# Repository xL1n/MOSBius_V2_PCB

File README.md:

MOSBius V2 PCB Design 
Contains Mother Board & Daughter Board

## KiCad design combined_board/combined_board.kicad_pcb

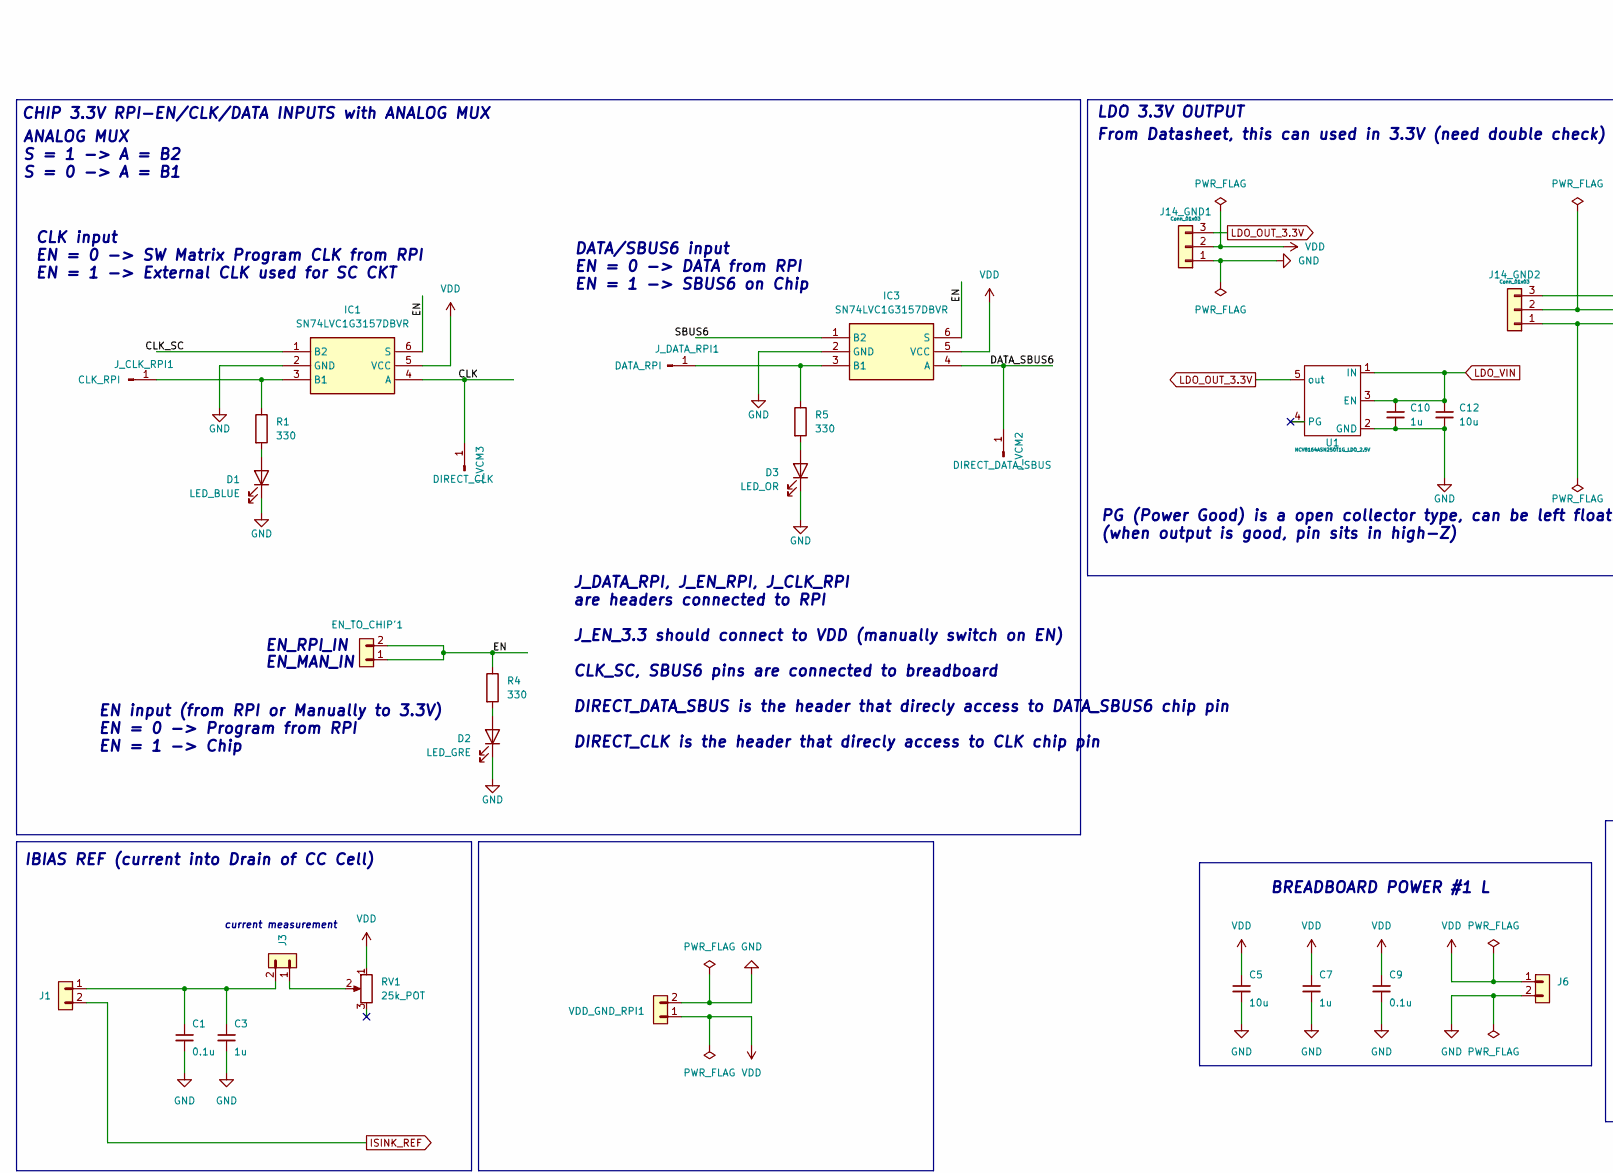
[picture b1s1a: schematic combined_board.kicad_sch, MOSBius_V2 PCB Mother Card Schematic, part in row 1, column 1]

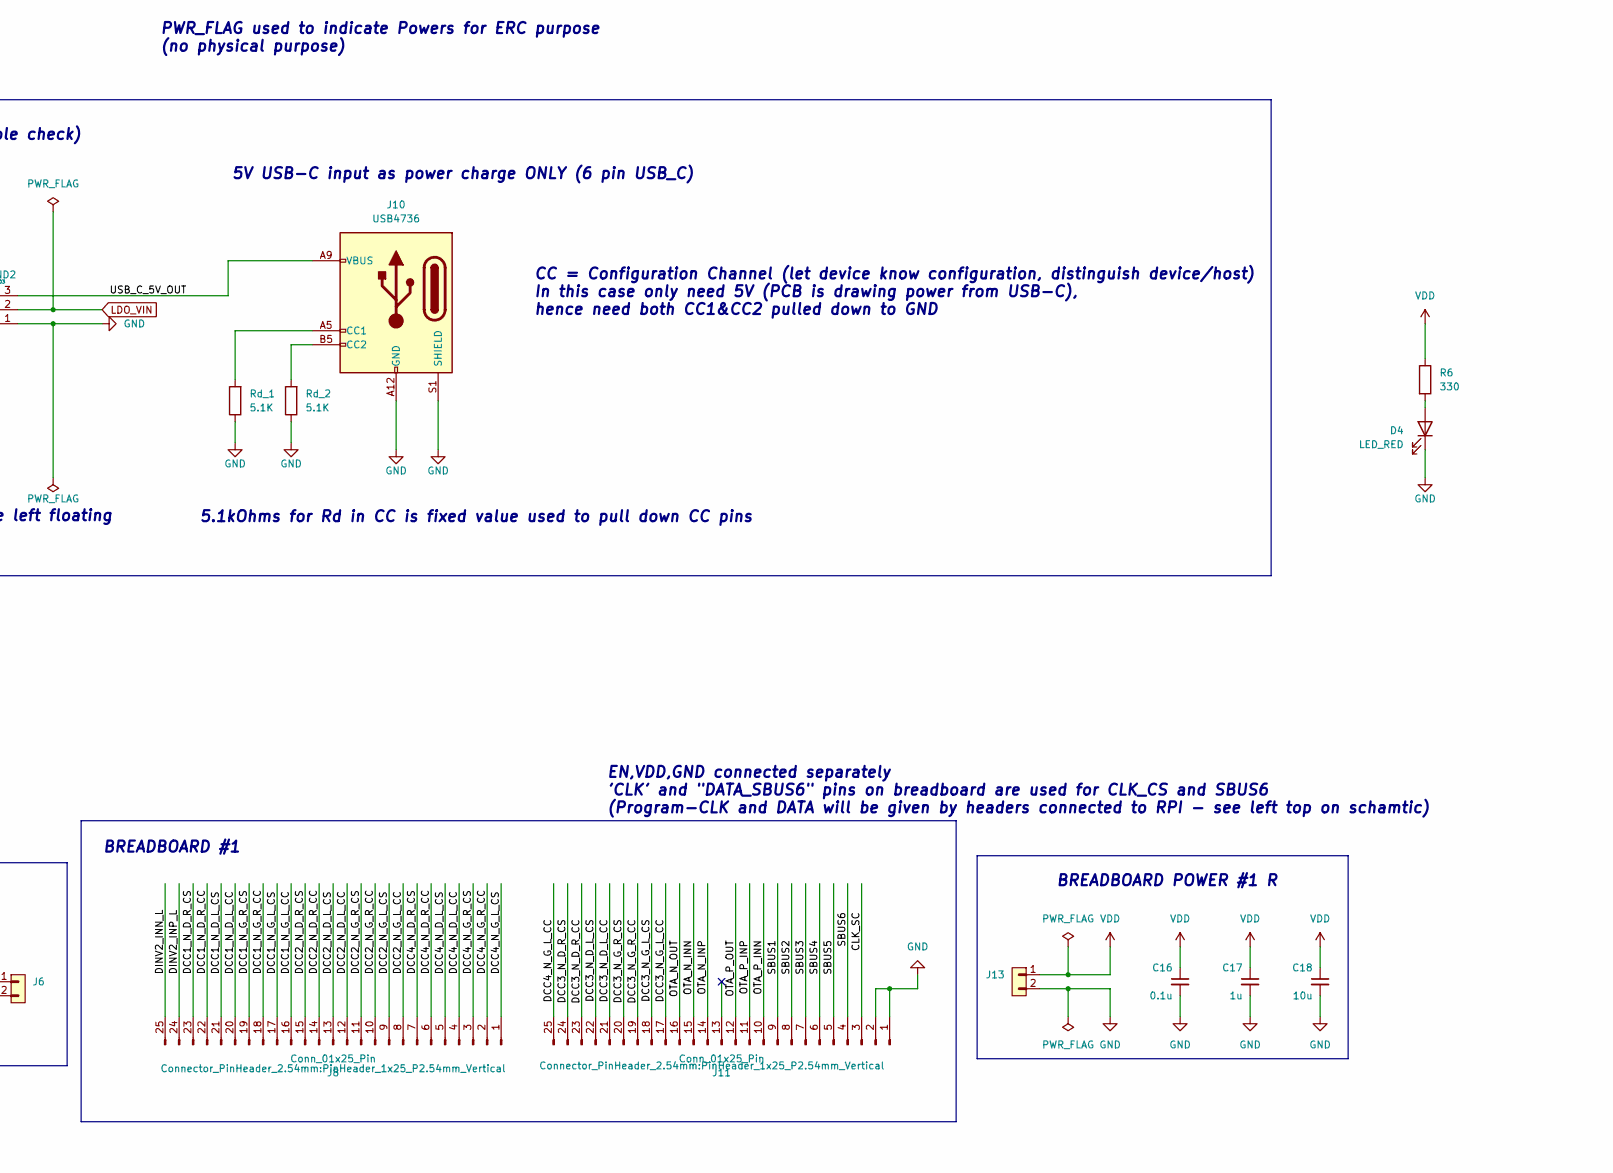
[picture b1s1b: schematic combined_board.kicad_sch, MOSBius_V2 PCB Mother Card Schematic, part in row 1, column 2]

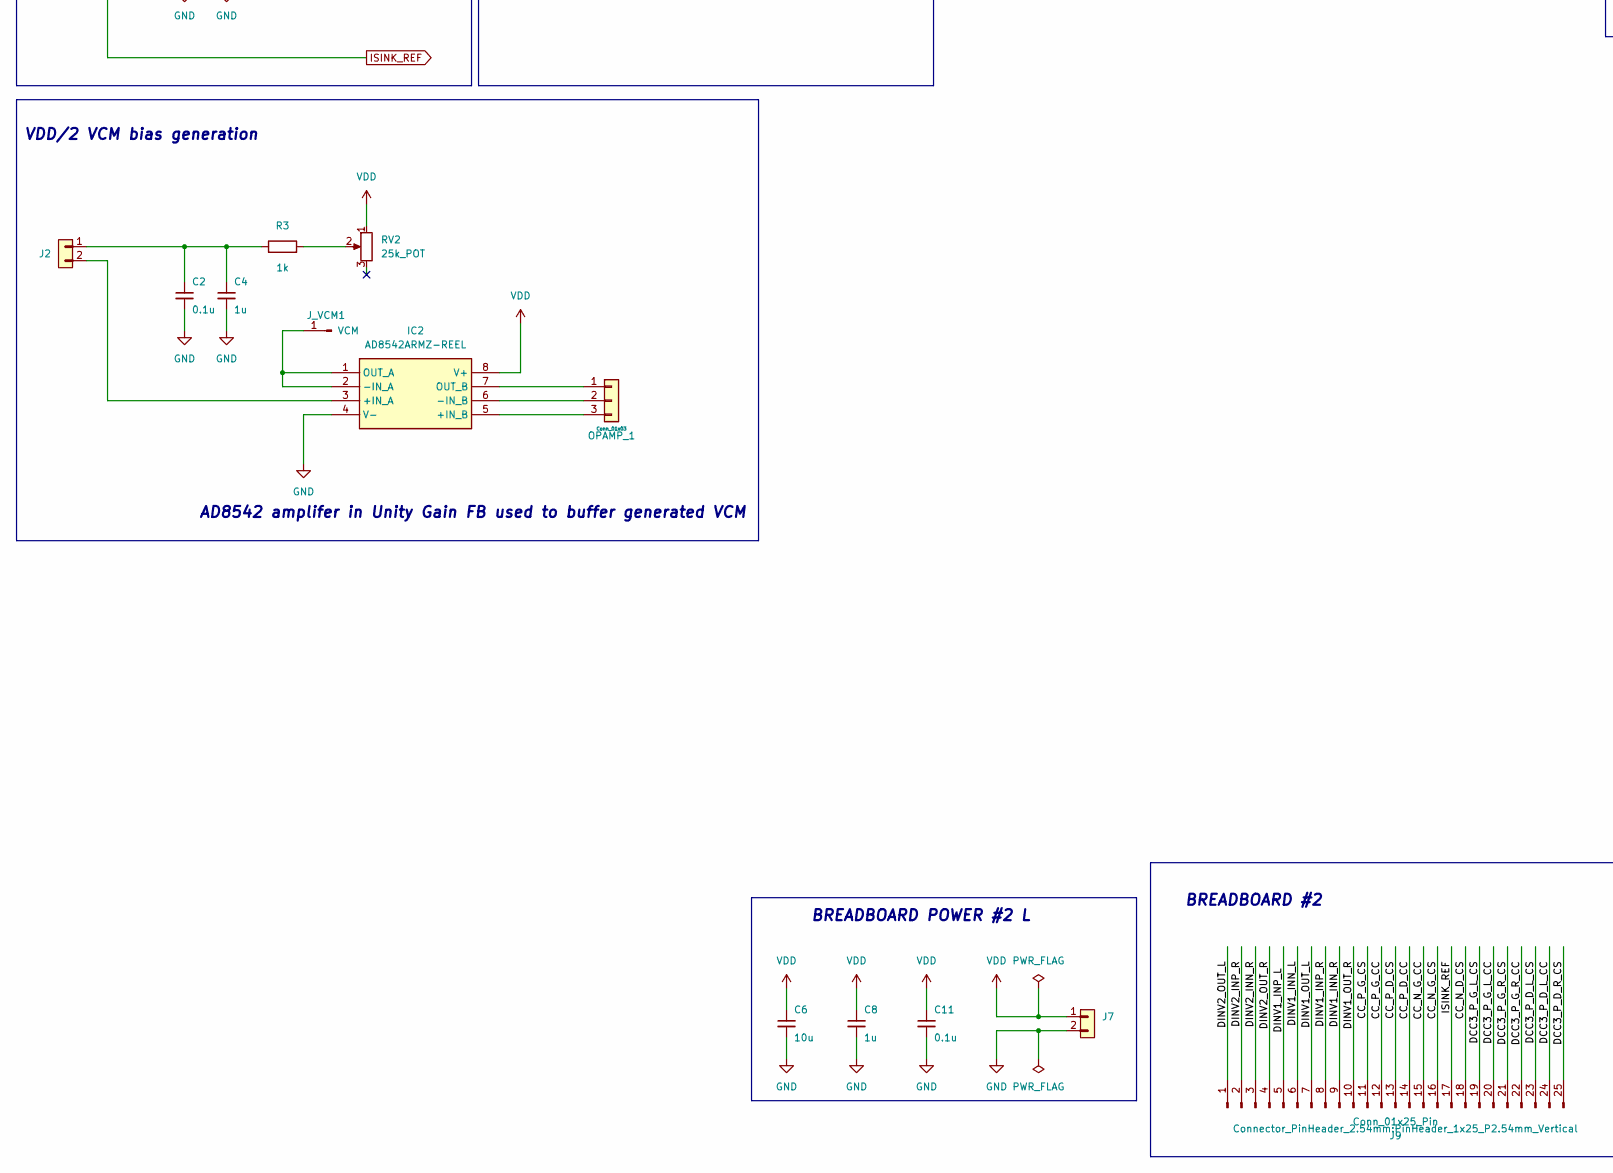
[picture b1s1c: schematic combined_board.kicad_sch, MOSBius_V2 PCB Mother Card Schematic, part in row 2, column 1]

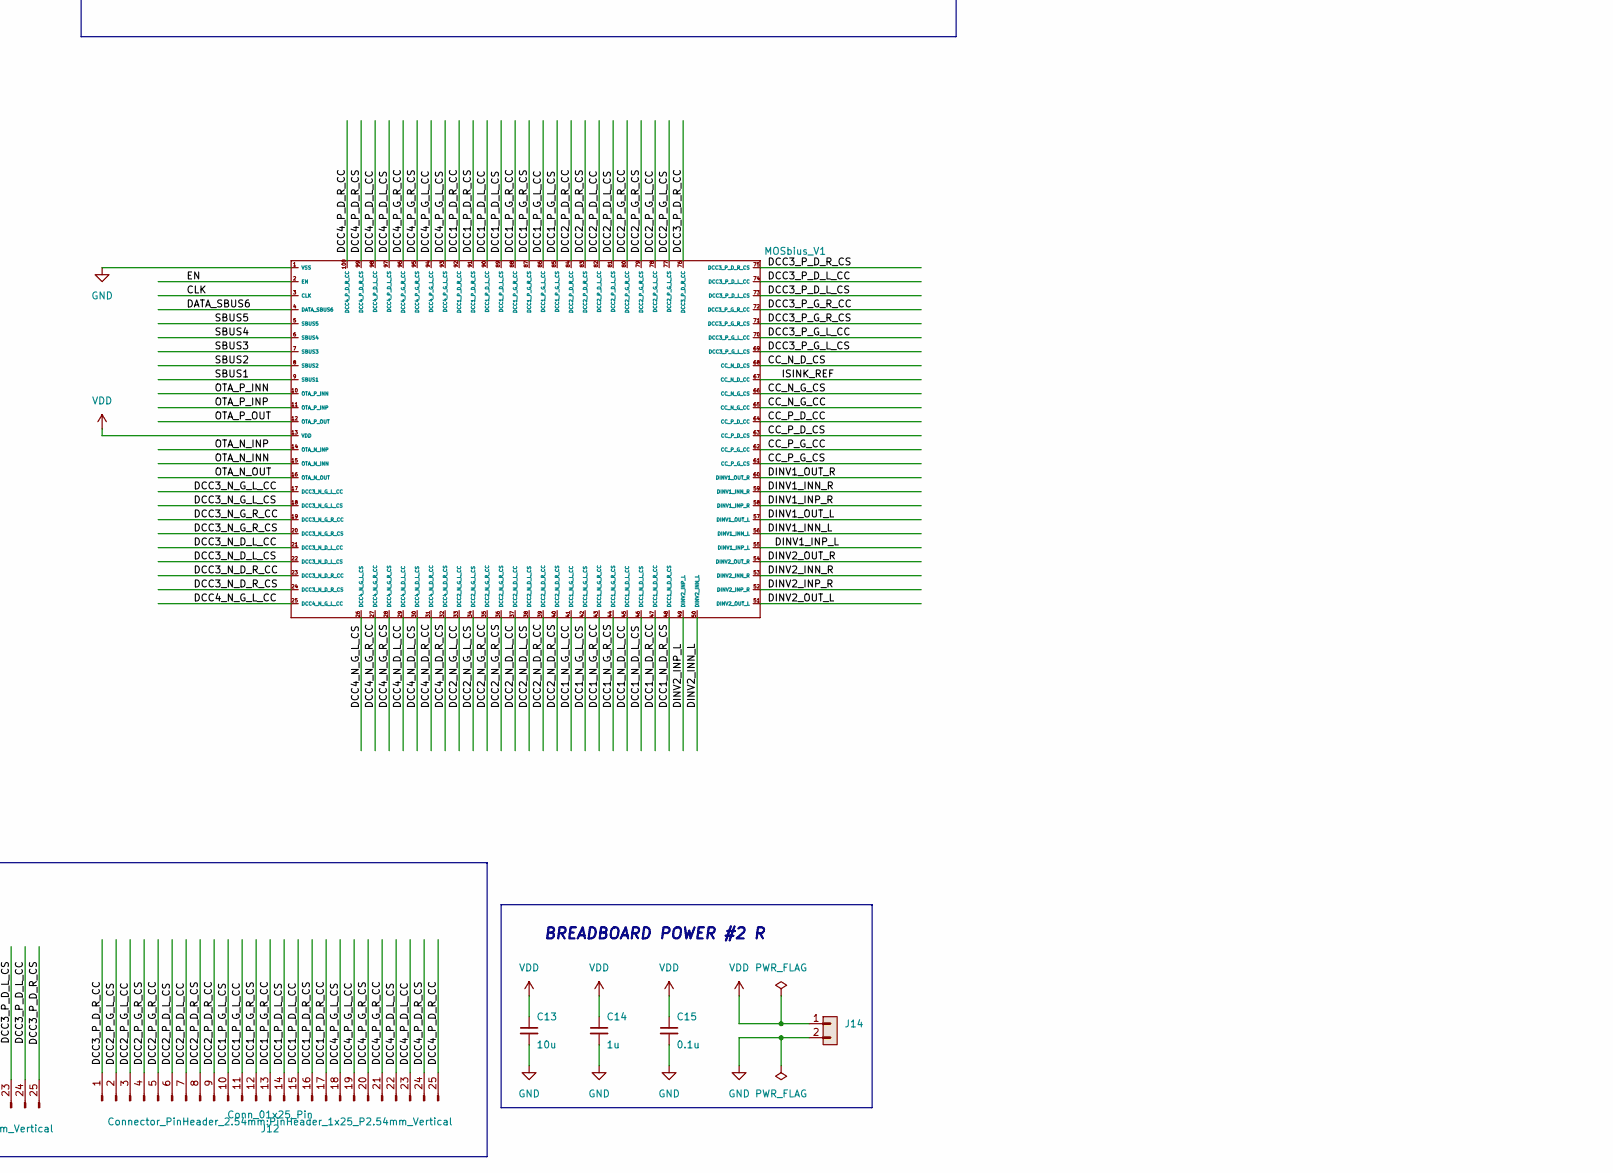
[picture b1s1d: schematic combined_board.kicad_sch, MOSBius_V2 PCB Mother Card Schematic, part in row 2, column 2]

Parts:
C1, C2, C9, C11, C15, C16: 0.1u; C_0603_1608Metric
C3, C4, C7, C8, C10, C14, C17: 1u; C_0603_1608Metric
C5, C6, C12, C13, C18: 10u; C_0603_1608Metric
D1: LED_BLUE; LED_150120RS75000_WRE
D2: LED_GRE; LED_150120RS75000_WRE
D3: LED_OR; LED_150120RS75000_WRE
D4: LED_RED; LED_150120RS75000_WRE
EN_TO_CHIP'1: PINHD_1x2_Male; PinHeader_1x02_P2.54mm_Vertical
IC1, IC3: SN74LVC1G3157DBVR; SN74LVC1G3157; Manufacturer_Part_Number SN74LVC1G3157DBVR; Mouser Part Number 595-SN74LVC1G3157DBV
IC2: AD8542ARMZ-REEL; AD8542; Manufacturer_Part_Number AD8542ARMZ-REEL; Mouser Part Number 584-AD8542ARMZ-R
J1, J2, J3, J6, J7, J14: PINHD_1x2_Male; PinHeader_1x02_P2.54mm_Vertical
J8, J9, J11, J12: Conn_01x25_Pin; PinHeader_1x25_P2.54mm_Vertical
J10: USB4736; USB_C_Receptacle_GCT_USB4125-xx-x_6P_TopMnt_Horizontal
J13: Conn_01x02_Pin; PinHeader_1x02_P2.54mm_Vertical
J14_GND1, J14_GND2: Conn_01x03; PinHeader_1x03_P2.54mm_Vertical
J_CLK_RPI1: CLK_RPI; PinHeader_1x01_P2.54mm_Vertical
J_DATA_RPI1: DATA_RPI; PinHeader_1x01_P2.54mm_Vertical
J_VCM1: VCM; PinHeader_1x01_P2.54mm_Vertical
J_VCM2: DIRECT_DATA_SBUS; PinHeader_1x01_P2.54mm_Vertical
J_VCM3: DIRECT_CLK; PinHeader_1x01_P2.54mm_Vertical
MOSbius_V1: MOSbius_V2; ArtInChip_QFN-100-1EP_12x12mm_P0.4mm_EP7.4x7.4mm
OPAMP_1: Conn_01x03; PinHeader_1x03_P2.54mm_Vertical
R1, R4, R5, R6: 330; R_0603_1608Metric
R3: 1k; R_0603_1608Metric
RV1, RV2: 25k_POT; Potentiometer_Bourns_3266Y_Vertical
Rd_1, Rd_2: 5.1K; R_0603_1608Metric
U1: NCV8164ASN250T1G_LDO_2.5V; NCV8164ASN250T1G_LDO
VDD_GND_RPI1: PINHD_1x2_Male; PinHeader_1x02_P2.54mm_Vertical

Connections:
/CC_N_D_CS: J9.18, MOSbius_V1.68 (CC_N_D_CS); also elsewhere on the board
/CC_N_G_CC: J9.15, MOSbius_V1.65 (CC_N_G_CC); also elsewhere on the board
/CC_N_G_CS: J9.16, MOSbius_V1.66 (CC_N_G_CS); also elsewhere on the board
/CC_P_D_CC: J9.14, MOSbius_V1.64 (CC_P_D_CC); also elsewhere on the board
/CC_P_D_CS: J9.13, MOSbius_V1.63 (CC_P_D_CS); also elsewhere on the board
/CC_P_G_CC: J9.12, MOSbius_V1.62 (CC_P_G_CC); also elsewhere on the board
/CC_P_G_CS: J9.11, MOSbius_V1.61 (CC_P_G_CS); also elsewhere on the board
/CLK: IC1.4 (A), J_VCM3.1, MOSbius_V1.3 (CLK); also elsewhere on the board
/CLK_SC: IC1.1 (B2), J11.3
/DATA_SBUS6: IC3.4 (A), J_VCM2.1, MOSbius_V1.4 (DATA_SBUS6); also elsewhere on the board
/DCC1_N_D_L_CC: J8.20, MOSbius_V1.45 (DCC1_N_D_L_CC); also elsewhere on the board
/DCC1_N_D_L_CS: J8.21, MOSbius_V1.46 (DCC1_N_D_L_CS); also elsewhere on the board
/DCC1_N_D_R_CC: J8.22, MOSbius_V1.47 (DCC1_N_D_R_CC); also elsewhere on the board
/DCC1_N_D_R_CS: J8.23, MOSbius_V1.48 (DCC1_N_D_R_CS); also elsewhere on the board
/DCC1_N_G_L_CC: J8.16, MOSbius_V1.41 (DCC1_N_G_L_CC); also elsewhere on the board
/DCC1_N_G_L_CS: J8.17, MOSbius_V1.42 (DCC1_N_G_L_CS); also elsewhere on the board
/DCC1_N_G_R_CC: J8.18, MOSbius_V1.43 (DCC1_N_G_R_CC); also elsewhere on the board
/DCC1_N_G_R_CS: J8.19, MOSbius_V1.44 (DCC1_N_G_R_CS); also elsewhere on the board
/DCC1_P_D_L_CC: J12.15, MOSbius_V1.90 (DCC1_P_D_L_CC); also elsewhere on the board
/DCC1_P_D_L_CS: J12.14, MOSbius_V1.89 (DCC1_P_D_L_CS); also elsewhere on the board
/DCC1_P_D_R_CC: J12.17, MOSbius_V1.92 (DCC1_P_D_R_CC); also elsewhere on the board
/DCC1_P_D_R_CS: J12.16, MOSbius_V1.91 (DCC1_P_D_R_CS); also elsewhere on the board
/DCC1_P_G_L_CC: J12.11, MOSbius_V1.86 (DCC1_P_G_L_CC); also elsewhere on the board
/DCC1_P_G_L_CS: J12.10, MOSbius_V1.85 (DCC1_P_G_L_CS); also elsewhere on the board
/DCC1_P_G_R_CC: J12.13, MOSbius_V1.88 (DCC1_P_G_R_CC); also elsewhere on the board
/DCC1_P_G_R_CS: J12.12, MOSbius_V1.87 (DCC1_P_G_R_CS); also elsewhere on the board
/DCC2_N_D_L_CC: J8.12, MOSbius_V1.37 (DCC2_N_D_L_CC); also elsewhere on the board
/DCC2_N_D_L_CS: J8.13, MOSbius_V1.38 (DCC2_N_D_L_CS); also elsewhere on the board
/DCC2_N_D_R_CC: J8.14, MOSbius_V1.39 (DCC2_N_D_R_CC); also elsewhere on the board
/DCC2_N_D_R_CS: J8.15, MOSbius_V1.40 (DCC2_N_D_R_CS); also elsewhere on the board
/DCC2_N_G_L_CC: J8.8, MOSbius_V1.33 (DCC2_N_G_L_CC); also elsewhere on the board
/DCC2_N_G_L_CS: J8.9, MOSbius_V1.34 (DCC2_N_G_L_CS); also elsewhere on the board
/DCC2_N_G_R_CC: J8.10, MOSbius_V1.35 (DCC2_N_G_R_CC); also elsewhere on the board
/DCC2_N_G_R_CS: J8.11, MOSbius_V1.36 (DCC2_N_G_R_CS); also elsewhere on the board
/DCC2_P_D_L_CC: J12.7, MOSbius_V1.82 (DCC2_P_D_L_CC); also elsewhere on the board
/DCC2_P_D_L_CS: J12.6, MOSbius_V1.81 (DCC2_P_D_L_CS); also elsewhere on the board
/DCC2_P_D_R_CC: J12.9, MOSbius_V1.84 (DCC2_P_D_R_CC); also elsewhere on the board
/DCC2_P_D_R_CS: J12.8, MOSbius_V1.83 (DCC2_P_D_R_CS); also elsewhere on the board
/DCC2_P_G_L_CC: J12.3, MOSbius_V1.78 (DCC2_P_G_L_CC); also elsewhere on the board
/DCC2_P_G_L_CS: J12.2, MOSbius_V1.77 (DCC2_P_G_L_CS); also elsewhere on the board
/DCC2_P_G_R_CC: J12.5, MOSbius_V1.80 (DCC2_P_G_R_CC); also elsewhere on the board
/DCC2_P_G_R_CS: J12.4, MOSbius_V1.79 (DCC2_P_G_R_CS); also elsewhere on the board
/DCC3_N_D_L_CC: J11.21, MOSbius_V1.21 (DCC3_N_D_L_CC); also elsewhere on the board
/DCC3_N_D_L_CS: J11.22, MOSbius_V1.22 (DCC3_N_D_L_CS); also elsewhere on the board
/DCC3_N_D_R_CC: J11.23, MOSbius_V1.23 (DCC3_N_D_R_CC); also elsewhere on the board
/DCC3_N_D_R_CS: J11.24, MOSbius_V1.24 (DCC3_N_D_R_CS); also elsewhere on the board
/DCC3_N_G_L_CC: J11.17, MOSbius_V1.17 (DCC3_N_G_L_CC); also elsewhere on the board
/DCC3_N_G_L_CS: J11.18, MOSbius_V1.18 (DCC3_N_G_L_CS); also elsewhere on the board
/DCC3_N_G_R_CC: J11.19, MOSbius_V1.19 (DCC3_N_G_R_CC); also elsewhere on the board
/DCC3_N_G_R_CS: J11.20, MOSbius_V1.20 (DCC3_N_G_R_CS); also elsewhere on the board
/DCC3_P_D_L_CC: J9.24, MOSbius_V1.74 (DCC3_P_D_L_CC); also elsewhere on the board
/DCC3_P_D_L_CS: J9.23, MOSbius_V1.73 (DCC3_P_D_L_CS); also elsewhere on the board
/DCC3_P_D_R_CC: J12.1, MOSbius_V1.76 (DCC3_P_D_R_CC); also elsewhere on the board
/DCC3_P_D_R_CS: J9.25, MOSbius_V1.75 (DCC3_P_D_R_CS); also elsewhere on the board
/DCC3_P_G_L_CC: J9.20, MOSbius_V1.70 (DCC3_P_G_L_CC); also elsewhere on the board
/DCC3_P_G_L_CS: J9.19, MOSbius_V1.69 (DCC3_P_G_L_CS); also elsewhere on the board
/DCC3_P_G_R_CC: J9.22, MOSbius_V1.72 (DCC3_P_G_R_CC); also elsewhere on the board
/DCC3_P_G_R_CS: J9.21, MOSbius_V1.71 (DCC3_P_G_R_CS); also elsewhere on the board
/DCC4_N_D_L_CC: J8.4, MOSbius_V1.29 (DCC4_N_D_L_CC); also elsewhere on the board
/DCC4_N_D_L_CS: J8.5, MOSbius_V1.30 (DCC4_N_D_L_CS); also elsewhere on the board
/DCC4_N_D_R_CC: J8.6, MOSbius_V1.31 (DCC4_N_D_R_CC); also elsewhere on the board
/DCC4_N_D_R_CS: J8.7, MOSbius_V1.32 (DCC4_N_D_R_CS); also elsewhere on the board
/DCC4_N_G_L_CC: J11.25, MOSbius_V1.25 (DCC4_N_G_L_CC); also elsewhere on the board
/DCC4_N_G_L_CS: J8.1, MOSbius_V1.26 (DCC4_N_G_L_CS); also elsewhere on the board
/DCC4_N_G_R_CC: J8.2, MOSbius_V1.27 (DCC4_N_G_R_CC); also elsewhere on the board
/DCC4_N_G_R_CS: J8.3, MOSbius_V1.28 (DCC4_N_G_R_CS); also elsewhere on the board
/DCC4_P_D_L_CC: J12.23, MOSbius_V1.98 (DCC4_P_D_L_CC); also elsewhere on the board
/DCC4_P_D_L_CS: J12.22, MOSbius_V1.97 (DCC4_P_D_L_CS); also elsewhere on the board
/DCC4_P_D_R_CC: J12.25, MOSbius_V1.100 (DCC4_P_D_R_CC); also elsewhere on the board
/DCC4_P_D_R_CS: J12.24, MOSbius_V1.99 (DCC4_P_D_R_CS); also elsewhere on the board
/DCC4_P_G_L_CC: J12.19, MOSbius_V1.94 (DCC4_P_G_L_CC); also elsewhere on the board
/DCC4_P_G_L_CS: J12.18, MOSbius_V1.93 (DCC4_P_G_L_CS); also elsewhere on the board
/DCC4_P_G_R_CC: J12.21, MOSbius_V1.96 (DCC4_P_G_R_CC); also elsewhere on the board
/DCC4_P_G_R_CS: J12.20, MOSbius_V1.95 (DCC4_P_G_R_CS); also elsewhere on the board
/DINV1_INN_L: J9.6, MOSbius_V1.56 (DINV1_INN_L); also elsewhere on the board
/DINV1_INN_R: J9.9, MOSbius_V1.59 (DINV1_INN_R); also elsewhere on the board
/DINV1_INP_L: J9.5, MOSbius_V1.55 (DINV1_INP_L); also elsewhere on the board
/DINV1_INP_R: J9.8, MOSbius_V1.58 (DINV1_INP_R); also elsewhere on the board
/DINV1_OUT_L: J9.7, MOSbius_V1.57 (DINV1_OUT_L); also elsewhere on the board
/DINV1_OUT_R: J9.10, MOSbius_V1.60 (DINV1_OUT_R); also elsewhere on the board
/DINV2_INN_L: J8.25, MOSbius_V1.50 (DINV2_INN_L); also elsewhere on the board
/DINV2_INN_R: J9.3, MOSbius_V1.53 (DINV2_INN_R); also elsewhere on the board
/DINV2_INP_L: J8.24, MOSbius_V1.49 (DINV2_INP_L); also elsewhere on the board
/DINV2_INP_R: J9.2, MOSbius_V1.52 (DINV2_INP_R); also elsewhere on the board
/DINV2_OUT_L: J9.1, MOSbius_V1.51 (DINV2_OUT_L); also elsewhere on the board
/DINV2_OUT_R: J9.4, MOSbius_V1.54 (DINV2_OUT_R); also elsewhere on the board
/EN: EN_TO_CHIP'1.1, EN_TO_CHIP'1.2, IC1.6 (S), IC3.6 (S), MOSbius_V1.2 (EN), R4.1; also elsewhere on the board
/OTA_N_INN: J11.15, MOSbius_V1.15 (OTA_N_INN); also elsewhere on the board
/OTA_N_INP: J11.14, MOSbius_V1.14 (OTA_N_INP); also elsewhere on the board
/OTA_N_OUT: J11.16, MOSbius_V1.16 (OTA_N_OUT); also elsewhere on the board
/OTA_P_INN: J11.10, MOSbius_V1.10 (OTA_P_INN); also elsewhere on the board
/OTA_P_INP: J11.11, MOSbius_V1.11 (OTA_P_INP); also elsewhere on the board
/OTA_P_OUT: J11.12, MOSbius_V1.12 (OTA_P_OUT); also elsewhere on the board
/SBUS1: J11.9, MOSbius_V1.9 (SBUS1); also elsewhere on the board
/SBUS2: J11.8, MOSbius_V1.8 (SBUS2); also elsewhere on the board
/SBUS3: J11.7, MOSbius_V1.7 (SBUS3); also elsewhere on the board
/SBUS4: J11.6, MOSbius_V1.6 (SBUS4); also elsewhere on the board
/SBUS5: J11.5, MOSbius_V1.5 (SBUS5); also elsewhere on the board
/SBUS6: IC3.1 (B2), J11.4
/USB_C_5V_OUT: J10.A9 (VBUS), J10.B9 (VBUS), J14_GND2.3
GND: C1.2, C2.2, C3.2, C4.2, C5.2, C6.2, C7.2, C8.2, C9.2, C10.2, C11.2, C12.2, C13.2, C14.2, C15.2, C16.2, C17.2, C18.2, D1.1 (K), D2.1 (K), D3.1 (K), D4.1 (K), IC1.2 (GND), IC2.4 (V-), IC3.2 (GND), J6.2, J7.2, J10.A12 (GND), J10.B12 (GND), J10.S1 (SHIELD), J11.1, J11.2, J13.2, J14.2, J14_GND1.1, J14_GND2.1, MOSbius_V1.1 (VSS), Rd_1.1, Rd_2.1, U1.2 (GND), VDD_GND_RPI1.2; also elsewhere on the board
ISINK_REF: J1.2, J9.17, MOSbius_V1.67 (CC_N_D_CC); also elsewhere on the board
LDO_OUT_3.3V: J14_GND1.3, U1.5 (out)
LDO_VIN: C10.1, C12.1, J14_GND2.2, U1.1 (IN), U1.3 (EN)
unnamed: C1.1, C3.1, J1.1, J3.2
unnamed: C2.1, C4.1, J2.1, R3.2
unnamed: D1.2 (A), R1.2
unnamed: D2.2 (A), R4.2
unnamed: D3.2 (A), R5.2
unnamed: D4.2 (A), R6.2
unnamed: IC1.3 (B1), J_CLK_RPI1.1, R1.1
unnamed: IC2.3 (+IN_A), J2.2
unnamed: IC2.5 (+IN_B), OPAMP_1.3
unnamed: IC2.1 (OUT_A), IC2.2 (-IN_A), J_VCM1.1
unnamed: IC2.6 (-IN_B), OPAMP_1.2
unnamed: IC2.7 (OUT_B), OPAMP_1.1
unnamed: IC3.3 (B1), J_DATA_RPI1.1, R5.1
unnamed: J3.1, RV1.2
unnamed: J10.A5 (CC1), Rd_1.2
unnamed: J10.B5 (CC2), Rd_2.2
unnamed: R3.1, RV2.2
VDD: C5.1, C6.1, C7.1, C8.1, C9.1, C11.1, C13.1, C14.1, C15.1, C16.1, C17.1, C18.1, IC1.5 (VCC), IC2.8 (V+), IC3.5 (VCC), J6.1, J7.1, J13.1, J14.1, J14_GND1.2, MOSbius_V1.13 (VDD), R6.1, RV1.1, RV2.1, VDD_GND_RPI1.1; also elsewhere on the board

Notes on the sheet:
BREADBOARD #2
LDO 3.3V OUTPUT
BREADBOARD POWER #2 R
CLK input EN = 0 -> SW Matrix Program CLK from RPI EN = 1 -> External CLK used for SC CKT
CC = Configuration Channel (let device know configuration, distinguish device/host) In this case only need 5V (PCB is drawing power from USB-C), hence need both CC1&CC2 pulled down to GND
EN_RPI_IN
AD8542 amplifer in Unity Gain FB used to buffer generated VCM
PWR_FLAG used to indicate Powers for ERC purpose (no physical purpose)
BREADBOARD #1
IBIAS REF (current into Drain of CC Cell)
BREADBOARD POWER #1 R
From Datasheet, this can used in 3.3V (need double check)
EN_MAN_IN
EN,VDD,GND connected separately 'CLK' and "DATA_SBUS6" pins on breadboard are used for CLK_CS and SBUS6 (Program-CLK and DATA will be given by headers connected to RPI - see left top on schamtic)
5V USB-C input as power charge ONLY (6 pin USB_C)
ANALOG MUX S = 1 -> A = B2 S = 0 -> A = B1
VDD/2 VCM bias generation
EN input (from RPI or Manually to 3.3V) EN = 0 -> Program from RPI EN = 1 -> Chip
J_DATA_RPI, J_EN_RPI, J_CLK_RPI are headers connected to RPI J_EN_3.3 should connect to VDD (manually switch on EN) CLK_SC, SBUS6 pins are connected to breadboard DIRECT_DATA_SBUS is the header that direcly access to DATA_SBUS6 chip pin DIRECT_CLK is the header that direcly access to CLK chip pin
BREADBOARD POWER #2 L
CHIP 3.3V RPI-EN/CLK/DATA INPUTS with ANALOG MUX
DATA/SBUS6 input EN = 0 -> DATA from RPI EN = 1 -> SBUS6 on Chip
BREADBOARD POWER #1 L
5.1kOhms for Rd in CC is fixed value used to pull down CC pins
current measurement
PG (Power Good) is a open collector type, can be left floating (when output is good, pin sits in high-Z)

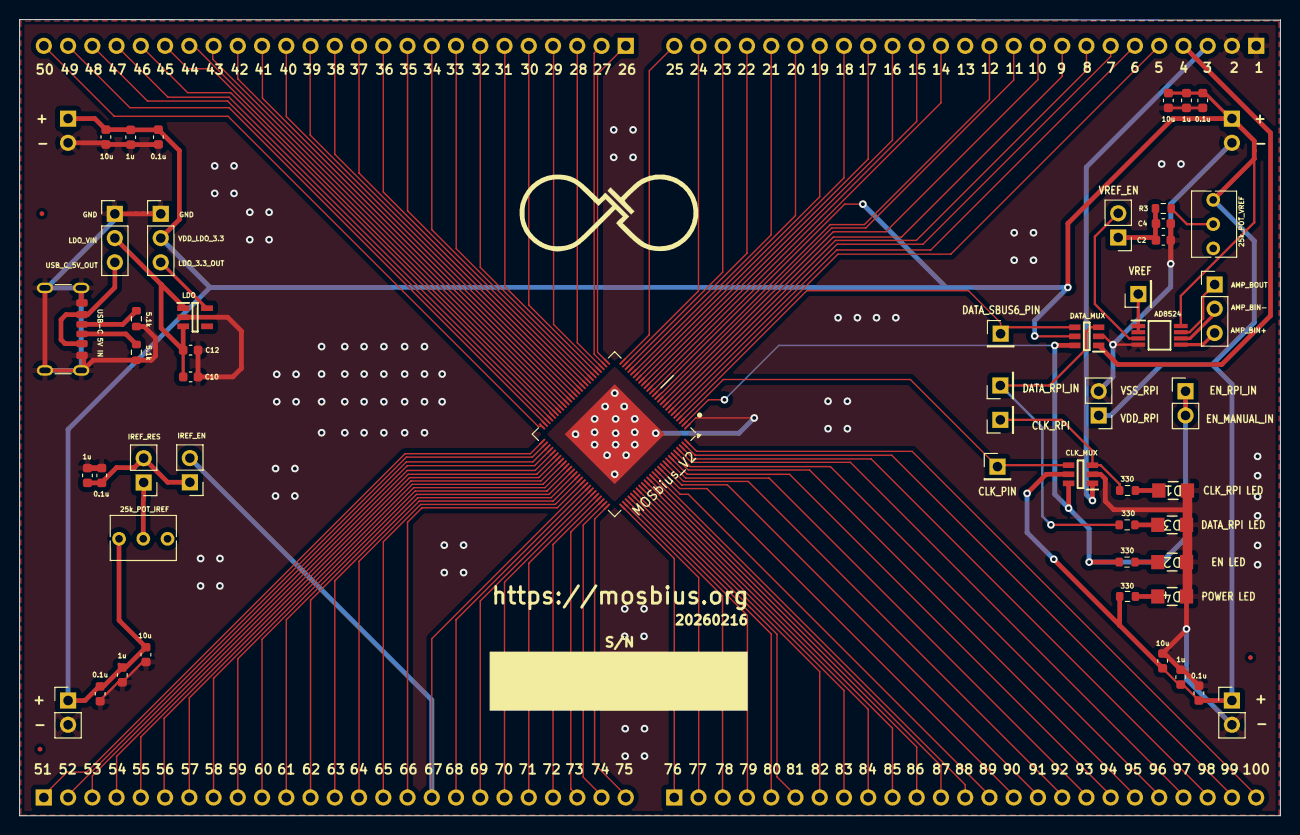
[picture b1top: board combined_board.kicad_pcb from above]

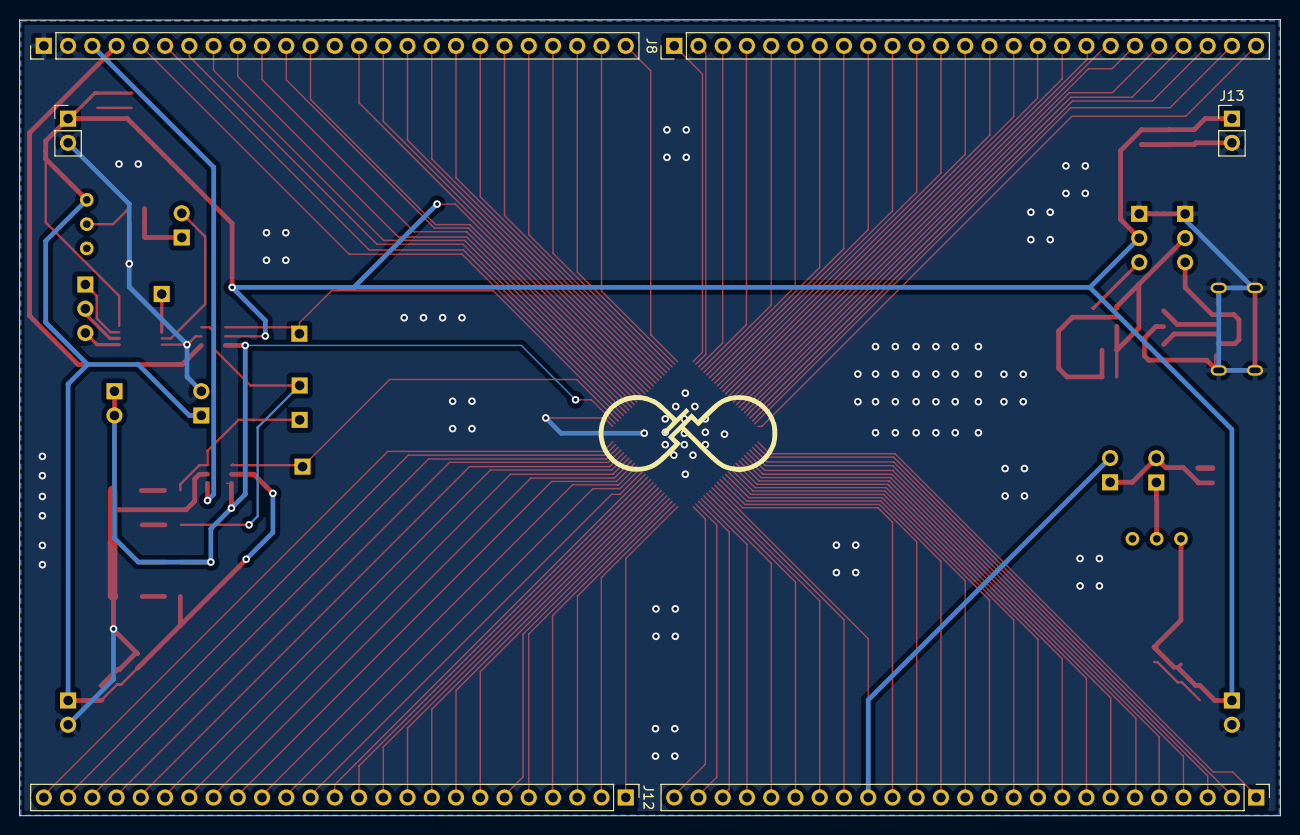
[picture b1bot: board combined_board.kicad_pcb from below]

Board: 2 copper layers, 132.1 x 83.4 mm, 58 parts (6 on the bottom side), 122 nets.

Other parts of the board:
MOSbius_V2: MOSbius_V2; ArtInChip_QFN-100-1EP_12x12mm_P0.4mm_EP7.4x7.4mm

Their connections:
/CC_N_D_CS: MOSbius_V2.68 (CC_N_D_CS); also elsewhere on the board
/CC_N_G_CC: MOSbius_V2.65 (CC_N_G_CC); also elsewhere on the board
/CC_N_G_CS: MOSbius_V2.66 (CC_N_G_CS); also elsewhere on the board
/CC_P_D_CC: MOSbius_V2.64 (CC_P_D_CC); also elsewhere on the board
/CC_P_D_CS: MOSbius_V2.63 (CC_P_D_CS); also elsewhere on the board
/CC_P_G_CC: MOSbius_V2.62 (CC_P_G_CC); also elsewhere on the board
/CC_P_G_CS: MOSbius_V2.61 (CC_P_G_CS); also elsewhere on the board
/CLK: MOSbius_V2.3 (CLK); also elsewhere on the board
/DATA_SBUS6: MOSbius_V2.4 (DATA_SBUS6); also elsewhere on the board
/DCC1_N_D_L_CC: MOSbius_V2.45 (DCC1_N_D_L_CC); also elsewhere on the board
/DCC1_N_D_L_CS: MOSbius_V2.46 (DCC1_N_D_L_CS); also elsewhere on the board
/DCC1_N_D_R_CC: MOSbius_V2.47 (DCC1_N_D_R_CC); also elsewhere on the board
/DCC1_N_D_R_CS: MOSbius_V2.48 (DCC1_N_D_R_CS); also elsewhere on the board
/DCC1_N_G_L_CC: MOSbius_V2.41 (DCC1_N_G_L_CC); also elsewhere on the board
/DCC1_N_G_L_CS: MOSbius_V2.42 (DCC1_N_G_L_CS); also elsewhere on the board
/DCC1_N_G_R_CC: MOSbius_V2.43 (DCC1_N_G_R_CC); also elsewhere on the board
/DCC1_N_G_R_CS: MOSbius_V2.44 (DCC1_N_G_R_CS); also elsewhere on the board
/DCC1_P_D_L_CC: MOSbius_V2.90 (DCC1_P_D_L_CC); also elsewhere on the board
/DCC1_P_D_L_CS: MOSbius_V2.89 (DCC1_P_D_L_CS); also elsewhere on the board
/DCC1_P_D_R_CC: MOSbius_V2.92 (DCC1_P_D_R_CC); also elsewhere on the board
/DCC1_P_D_R_CS: MOSbius_V2.91 (DCC1_P_D_R_CS); also elsewhere on the board
/DCC1_P_G_L_CC: MOSbius_V2.86 (DCC1_P_G_L_CC); also elsewhere on the board
/DCC1_P_G_L_CS: MOSbius_V2.85 (DCC1_P_G_L_CS); also elsewhere on the board
/DCC1_P_G_R_CC: MOSbius_V2.88 (DCC1_P_G_R_CC); also elsewhere on the board
/DCC1_P_G_R_CS: MOSbius_V2.87 (DCC1_P_G_R_CS); also elsewhere on the board
/DCC2_N_D_L_CC: MOSbius_V2.37 (DCC2_N_D_L_CC); also elsewhere on the board
/DCC2_N_D_L_CS: MOSbius_V2.38 (DCC2_N_D_L_CS); also elsewhere on the board
/DCC2_N_D_R_CC: MOSbius_V2.39 (DCC2_N_D_R_CC); also elsewhere on the board
/DCC2_N_D_R_CS: MOSbius_V2.40 (DCC2_N_D_R_CS); also elsewhere on the board
/DCC2_N_G_L_CC: MOSbius_V2.33 (DCC2_N_G_L_CC); also elsewhere on the board
/DCC2_N_G_L_CS: MOSbius_V2.34 (DCC2_N_G_L_CS); also elsewhere on the board
/DCC2_N_G_R_CC: MOSbius_V2.35 (DCC2_N_G_R_CC); also elsewhere on the board
/DCC2_N_G_R_CS: MOSbius_V2.36 (DCC2_N_G_R_CS); also elsewhere on the board
/DCC2_P_D_L_CC: MOSbius_V2.82 (DCC2_P_D_L_CC); also elsewhere on the board
/DCC2_P_D_L_CS: MOSbius_V2.81 (DCC2_P_D_L_CS); also elsewhere on the board
/DCC2_P_D_R_CC: MOSbius_V2.84 (DCC2_P_D_R_CC); also elsewhere on the board
/DCC2_P_D_R_CS: MOSbius_V2.83 (DCC2_P_D_R_CS); also elsewhere on the board
/DCC2_P_G_L_CC: MOSbius_V2.78 (DCC2_P_G_L_CC); also elsewhere on the board
/DCC2_P_G_L_CS: MOSbius_V2.77 (DCC2_P_G_L_CS); also elsewhere on the board
/DCC2_P_G_R_CC: MOSbius_V2.80 (DCC2_P_G_R_CC); also elsewhere on the board
/DCC2_P_G_R_CS: MOSbius_V2.79 (DCC2_P_G_R_CS); also elsewhere on the board
/DCC3_N_D_L_CC: MOSbius_V2.21 (DCC3_N_D_L_CC); also elsewhere on the board
/DCC3_N_D_L_CS: MOSbius_V2.22 (DCC3_N_D_L_CS); also elsewhere on the board
/DCC3_N_D_R_CC: MOSbius_V2.23 (DCC3_N_D_R_CC); also elsewhere on the board
/DCC3_N_D_R_CS: MOSbius_V2.24 (DCC3_N_D_R_CS); also elsewhere on the board
/DCC3_N_G_L_CC: MOSbius_V2.17 (DCC3_N_G_L_CC); also elsewhere on the board
/DCC3_N_G_L_CS: MOSbius_V2.18 (DCC3_N_G_L_CS); also elsewhere on the board
/DCC3_N_G_R_CC: MOSbius_V2.19 (DCC3_N_G_R_CC); also elsewhere on the board
/DCC3_N_G_R_CS: MOSbius_V2.20 (DCC3_N_G_R_CS); also elsewhere on the board
/DCC3_P_D_L_CC: MOSbius_V2.74 (DCC3_P_D_L_CC); also elsewhere on the board
/DCC3_P_D_L_CS: MOSbius_V2.73 (DCC3_P_D_L_CS); also elsewhere on the board
/DCC3_P_D_R_CC: MOSbius_V2.76 (DCC3_P_D_R_CC); also elsewhere on the board
/DCC3_P_D_R_CS: MOSbius_V2.75 (DCC3_P_D_R_CS); also elsewhere on the board
/DCC3_P_G_L_CC: MOSbius_V2.70 (DCC3_P_G_L_CC); also elsewhere on the board
/DCC3_P_G_L_CS: MOSbius_V2.69 (DCC3_P_G_L_CS); also elsewhere on the board
/DCC3_P_G_R_CC: MOSbius_V2.72 (DCC3_P_G_R_CC); also elsewhere on the board
/DCC3_P_G_R_CS: MOSbius_V2.71 (DCC3_P_G_R_CS); also elsewhere on the board
/DCC4_N_D_L_CC: MOSbius_V2.29 (DCC4_N_D_L_CC); also elsewhere on the board
/DCC4_N_D_L_CS: MOSbius_V2.30 (DCC4_N_D_L_CS); also elsewhere on the board
/DCC4_N_D_R_CC: MOSbius_V2.31 (DCC4_N_D_R_CC); also elsewhere on the board
/DCC4_N_D_R_CS: MOSbius_V2.32 (DCC4_N_D_R_CS); also elsewhere on the board
/DCC4_N_G_L_CC: MOSbius_V2.25 (DCC4_N_G_L_CC); also elsewhere on the board
/DCC4_N_G_L_CS: MOSbius_V2.26 (DCC4_N_G_L_CS); also elsewhere on the board
/DCC4_N_G_R_CC: MOSbius_V2.27 (DCC4_N_G_R_CC); also elsewhere on the board
/DCC4_N_G_R_CS: MOSbius_V2.28 (DCC4_N_G_R_CS); also elsewhere on the board
/DCC4_P_D_L_CC: MOSbius_V2.98 (DCC4_P_D_L_CC); also elsewhere on the board
/DCC4_P_D_L_CS: MOSbius_V2.97 (DCC4_P_D_L_CS); also elsewhere on the board
/DCC4_P_D_R_CC: MOSbius_V2.100 (DCC4_P_D_R_CC); also elsewhere on the board
/DCC4_P_D_R_CS: MOSbius_V2.99 (DCC4_P_D_R_CS); also elsewhere on the board
/DCC4_P_G_L_CC: MOSbius_V2.94 (DCC4_P_G_L_CC); also elsewhere on the board
/DCC4_P_G_L_CS: MOSbius_V2.93 (DCC4_P_G_L_CS); also elsewhere on the board
/DCC4_P_G_R_CC: MOSbius_V2.96 (DCC4_P_G_R_CC); also elsewhere on the board
/DCC4_P_G_R_CS: MOSbius_V2.95 (DCC4_P_G_R_CS); also elsewhere on the board
/DINV1_INN_L: MOSbius_V2.56 (DINV1_INN_L); also elsewhere on the board
/DINV1_INN_R: MOSbius_V2.59 (DINV1_INN_R); also elsewhere on the board
/DINV1_INP_L: MOSbius_V2.55 (DINV1_INP_L); also elsewhere on the board
/DINV1_INP_R: MOSbius_V2.58 (DINV1_INP_R); also elsewhere on the board
/DINV1_OUT_L: MOSbius_V2.57 (DINV1_OUT_L); also elsewhere on the board
/DINV1_OUT_R: MOSbius_V2.60 (DINV1_OUT_R); also elsewhere on the board
/DINV2_INN_L: MOSbius_V2.50 (DINV2_INN_L); also elsewhere on the board
/DINV2_INN_R: MOSbius_V2.53 (DINV2_INN_R); also elsewhere on the board
/DINV2_INP_L: MOSbius_V2.49 (DINV2_INP_L); also elsewhere on the board
/DINV2_INP_R: MOSbius_V2.52 (DINV2_INP_R); also elsewhere on the board
/DINV2_OUT_L: MOSbius_V2.51 (DINV2_OUT_L); also elsewhere on the board
/DINV2_OUT_R: MOSbius_V2.54 (DINV2_OUT_R); also elsewhere on the board
/EN: MOSbius_V2.2 (EN); also elsewhere on the board
/OTA_N_INN: MOSbius_V2.15 (OTA_N_INN); also elsewhere on the board
/OTA_N_INP: MOSbius_V2.14 (OTA_N_INP); also elsewhere on the board
/OTA_N_OUT: MOSbius_V2.16 (OTA_N_OUT); also elsewhere on the board
/OTA_P_INN: MOSbius_V2.10 (OTA_P_INN); also elsewhere on the board
/OTA_P_INP: MOSbius_V2.11 (OTA_P_INP); also elsewhere on the board
/OTA_P_OUT: MOSbius_V2.12 (OTA_P_OUT); also elsewhere on the board
/SBUS1: MOSbius_V2.9 (SBUS1); also elsewhere on the board
/SBUS2: MOSbius_V2.8 (SBUS2); also elsewhere on the board
/SBUS3: MOSbius_V2.7 (SBUS3); also elsewhere on the board
/SBUS4: MOSbius_V2.6 (SBUS4); also elsewhere on the board
/SBUS5: MOSbius_V2.5 (SBUS5); also elsewhere on the board
GND: MOSbius_V2.1 (VSS); also elsewhere on the board
ISINK_REF: MOSbius_V2.67 (CC_N_D_CC); also elsewhere on the board
VDD: MOSbius_V2.13 (VDD); also elsewhere on the board
